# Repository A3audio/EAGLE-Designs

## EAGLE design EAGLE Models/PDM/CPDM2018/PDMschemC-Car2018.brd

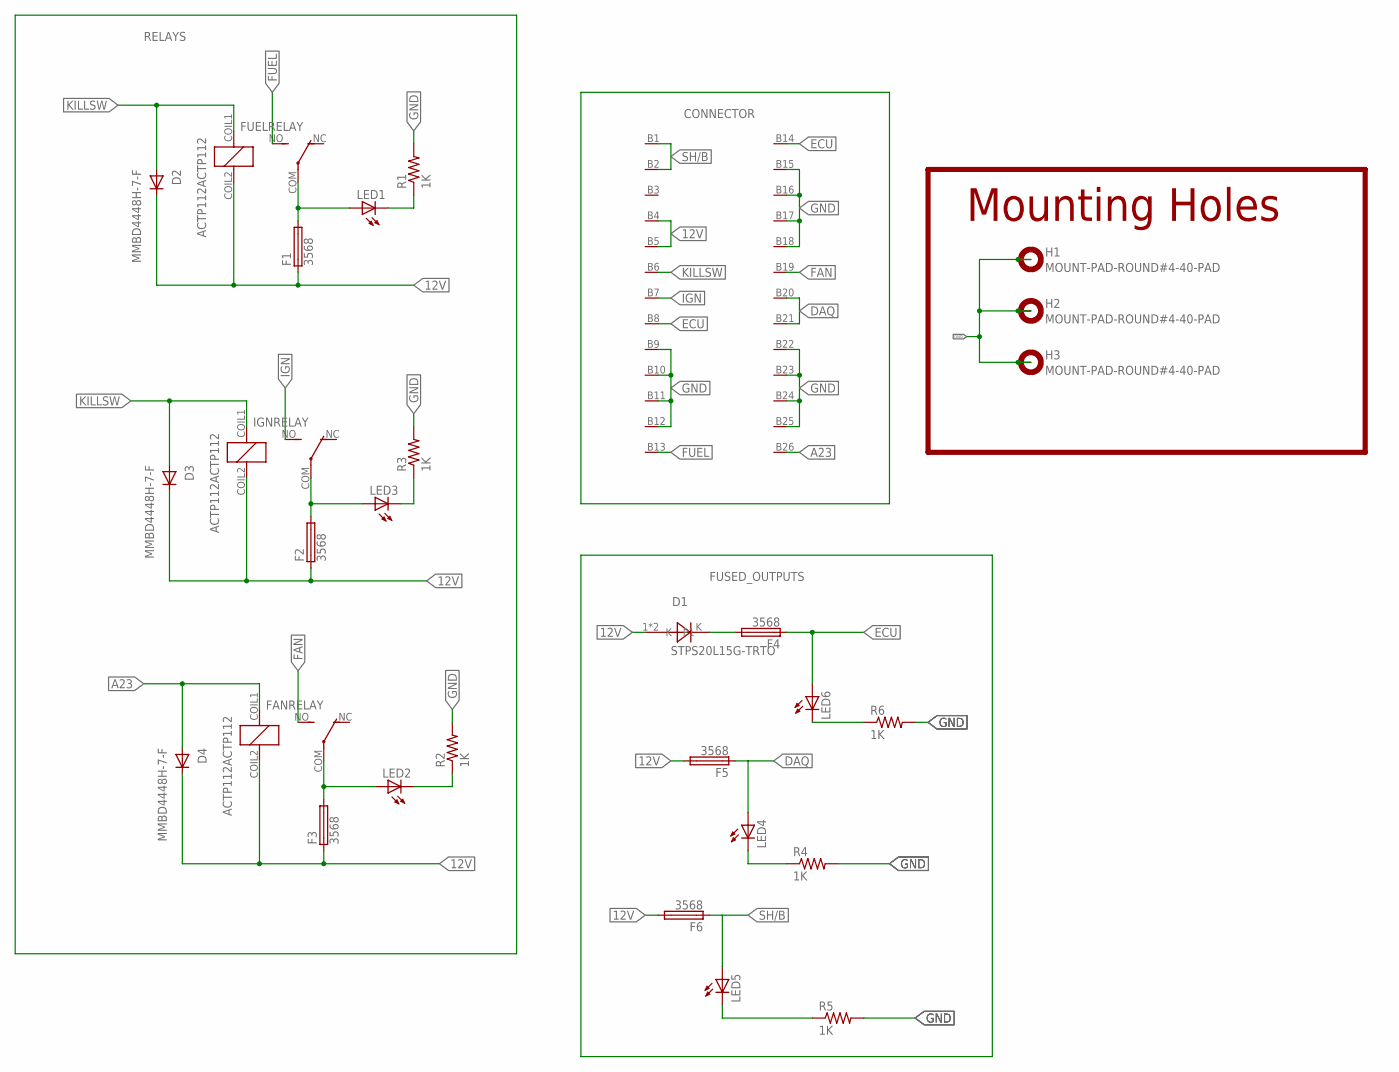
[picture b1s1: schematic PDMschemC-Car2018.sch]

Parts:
D1: STPS20L15G-TRTO; TO-262DIODE
D2, D3, D4: MMBD4448H-7-F; SOT23-3
F1, F2, F3, F4, F5, F6: 3568
FANRELAY: ACTP112ACTP112; ACTP112
FUELRELAY: ACTP112ACTP112; ACTP112
H1, H2, H3: MOUNT-PAD-ROUND#4-40-PAD; #4-40-PAD-ROUND
IGNRELAY: ACTP112ACTP112; ACTP112
LED1, LED2, LED3, LED4, LED5, LED6: LEDCHIPLED_0805; CHIPLED_0805
R1, R2, R3, R4, R5, R6: 1K; R0805
U$1: SUPERSEAL1.0_26POS

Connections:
12V: D1.1, D1.2 (P1), D2.3 (C), D3.3 (C), D4.3 (C), F1.1, F1.2 (1), F2.1, F2.2 (1), F3.1, F3.2 (1), F5.3 (2), F5.4 (2), F6.3 (2), F6.4 (2), FANRELAY.COIL2, FUELRELAY.COIL2, IGNRELAY.COIL2, U$1.B4, U$1.B5
A23: D4.1 (A), FANRELAY.COIL1, U$1.B26
DAQ: F5.1, F5.2 (1), LED4.A, U$1.B20, U$1.B21
ECU: F4.1, F4.2 (1), LED6.A, U$1.B8, U$1.B14
FAN: FANRELAY.NO, U$1.B19
FUEL: FUELRELAY.NO, U$1.B13
GND: H1.P$1, H2.P$1, H3.P$1, R1.2, R2.2, R3.2, R4.2, R5.2, R6.2, U$1.B9, U$1.B10, U$1.B11, U$1.B12, U$1.B15, U$1.B16, U$1.B17, U$1.B18, U$1.B22, U$1.B23, U$1.B24, U$1.B25
IGN: IGNRELAY.NO, U$1.B7
KILLSW: D2.1 (A), D3.1 (A), FUELRELAY.COIL1, IGNRELAY.COIL1, U$1.B6
unnamed: F3.3 (2), F3.4 (2), FANRELAY.COM, LED2.A
unnamed: LED1.C, R1.1
unnamed: F1.3 (2), F1.4 (2), FUELRELAY.COM, LED1.A
unnamed: LED2.C, R2.1
unnamed: LED3.C, R3.1
unnamed: F2.3 (2), F2.4 (2), IGNRELAY.COM, LED3.A
unnamed: LED4.C, R4.1
unnamed: LED6.C, R6.1
unnamed: D1.K, F4.3 (2), F4.4 (2)
unnamed: LED5.C, R5.1
SH/B: F6.1, F6.2 (1), LED5.A, U$1.B1, U$1.B2

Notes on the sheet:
Mounting Holes

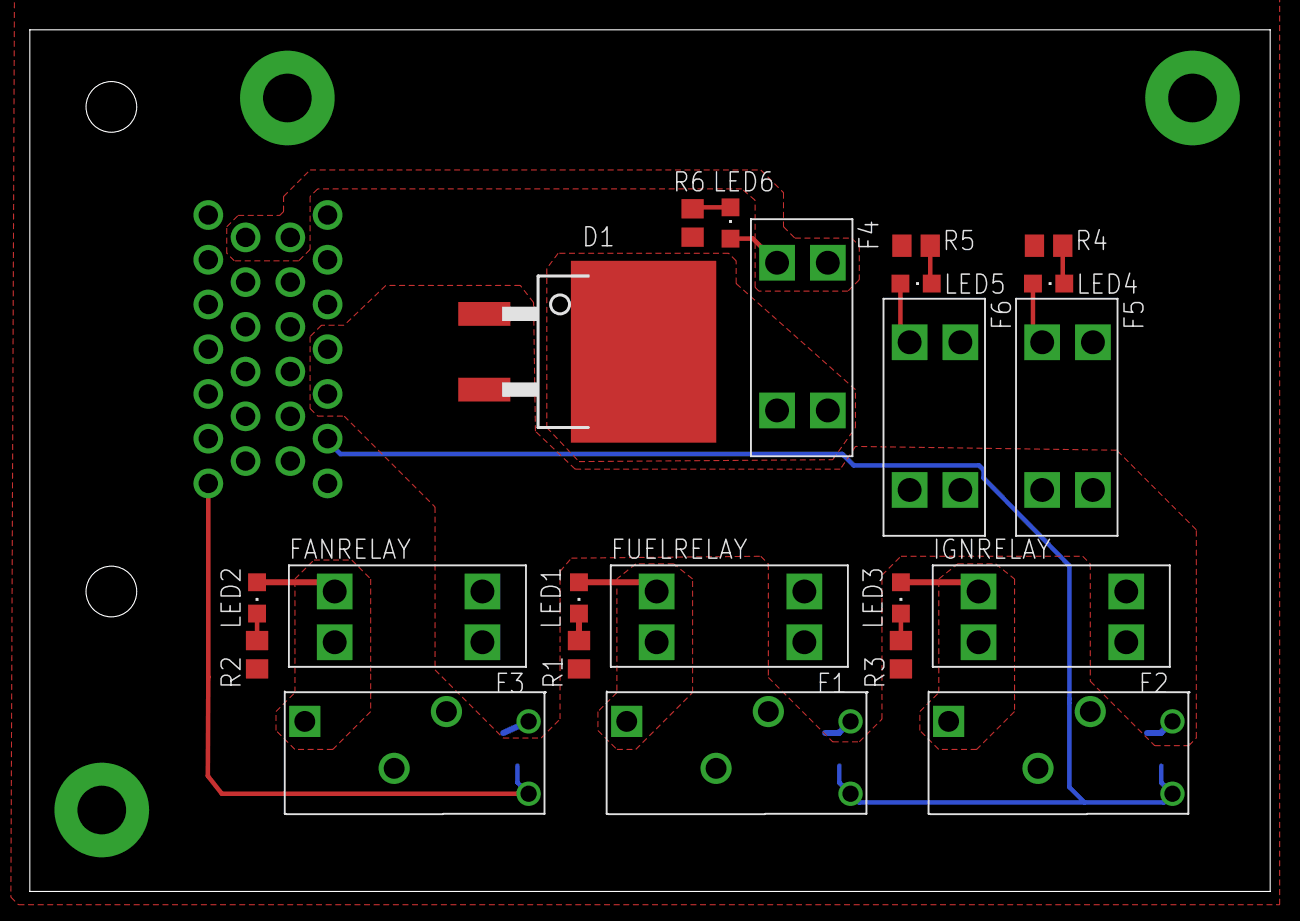
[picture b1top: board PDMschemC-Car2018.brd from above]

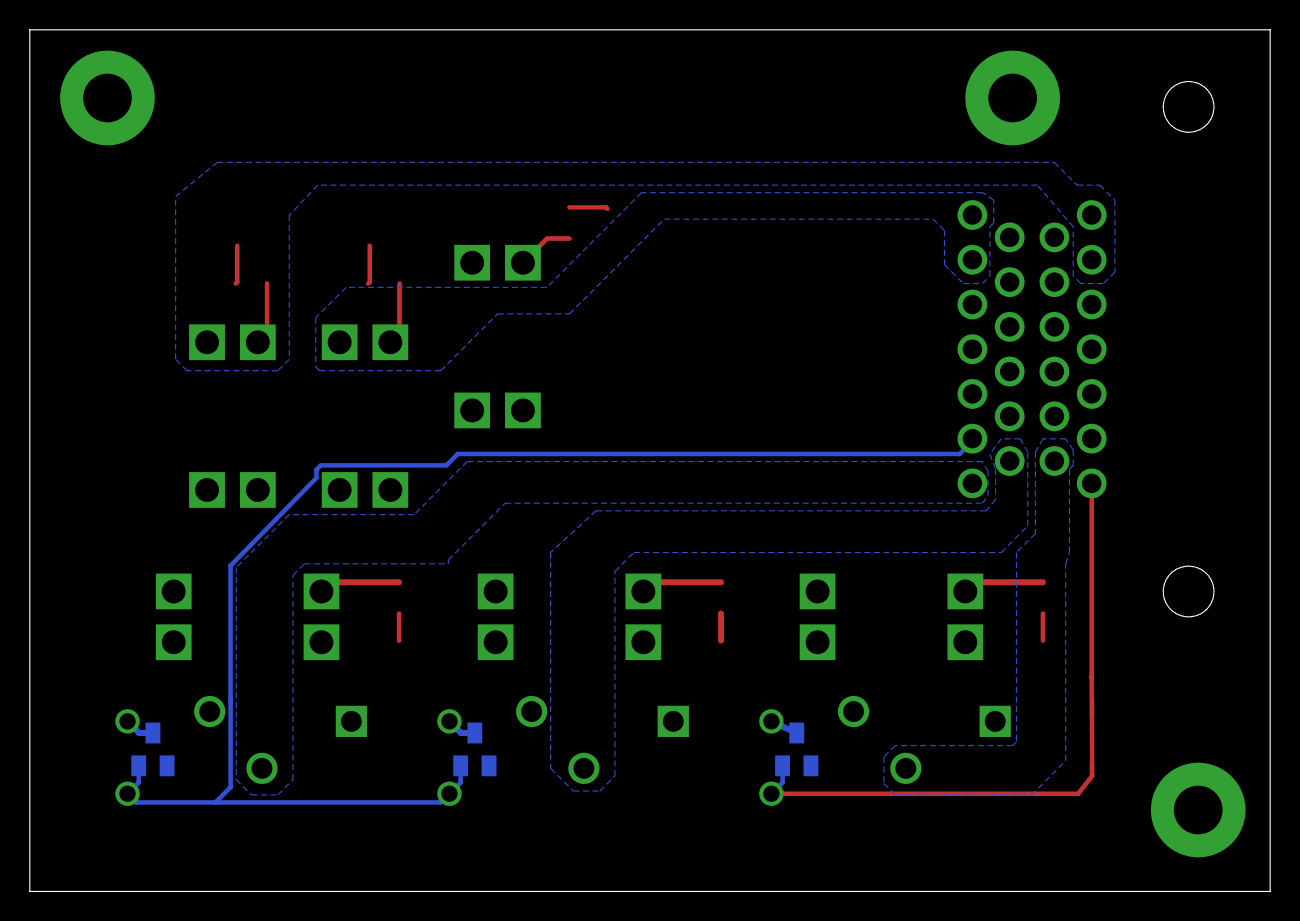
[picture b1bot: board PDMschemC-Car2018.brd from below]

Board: 2 copper layers, 83.2 x 57.8 mm, 29 parts (3 on the bottom side), 20 nets.

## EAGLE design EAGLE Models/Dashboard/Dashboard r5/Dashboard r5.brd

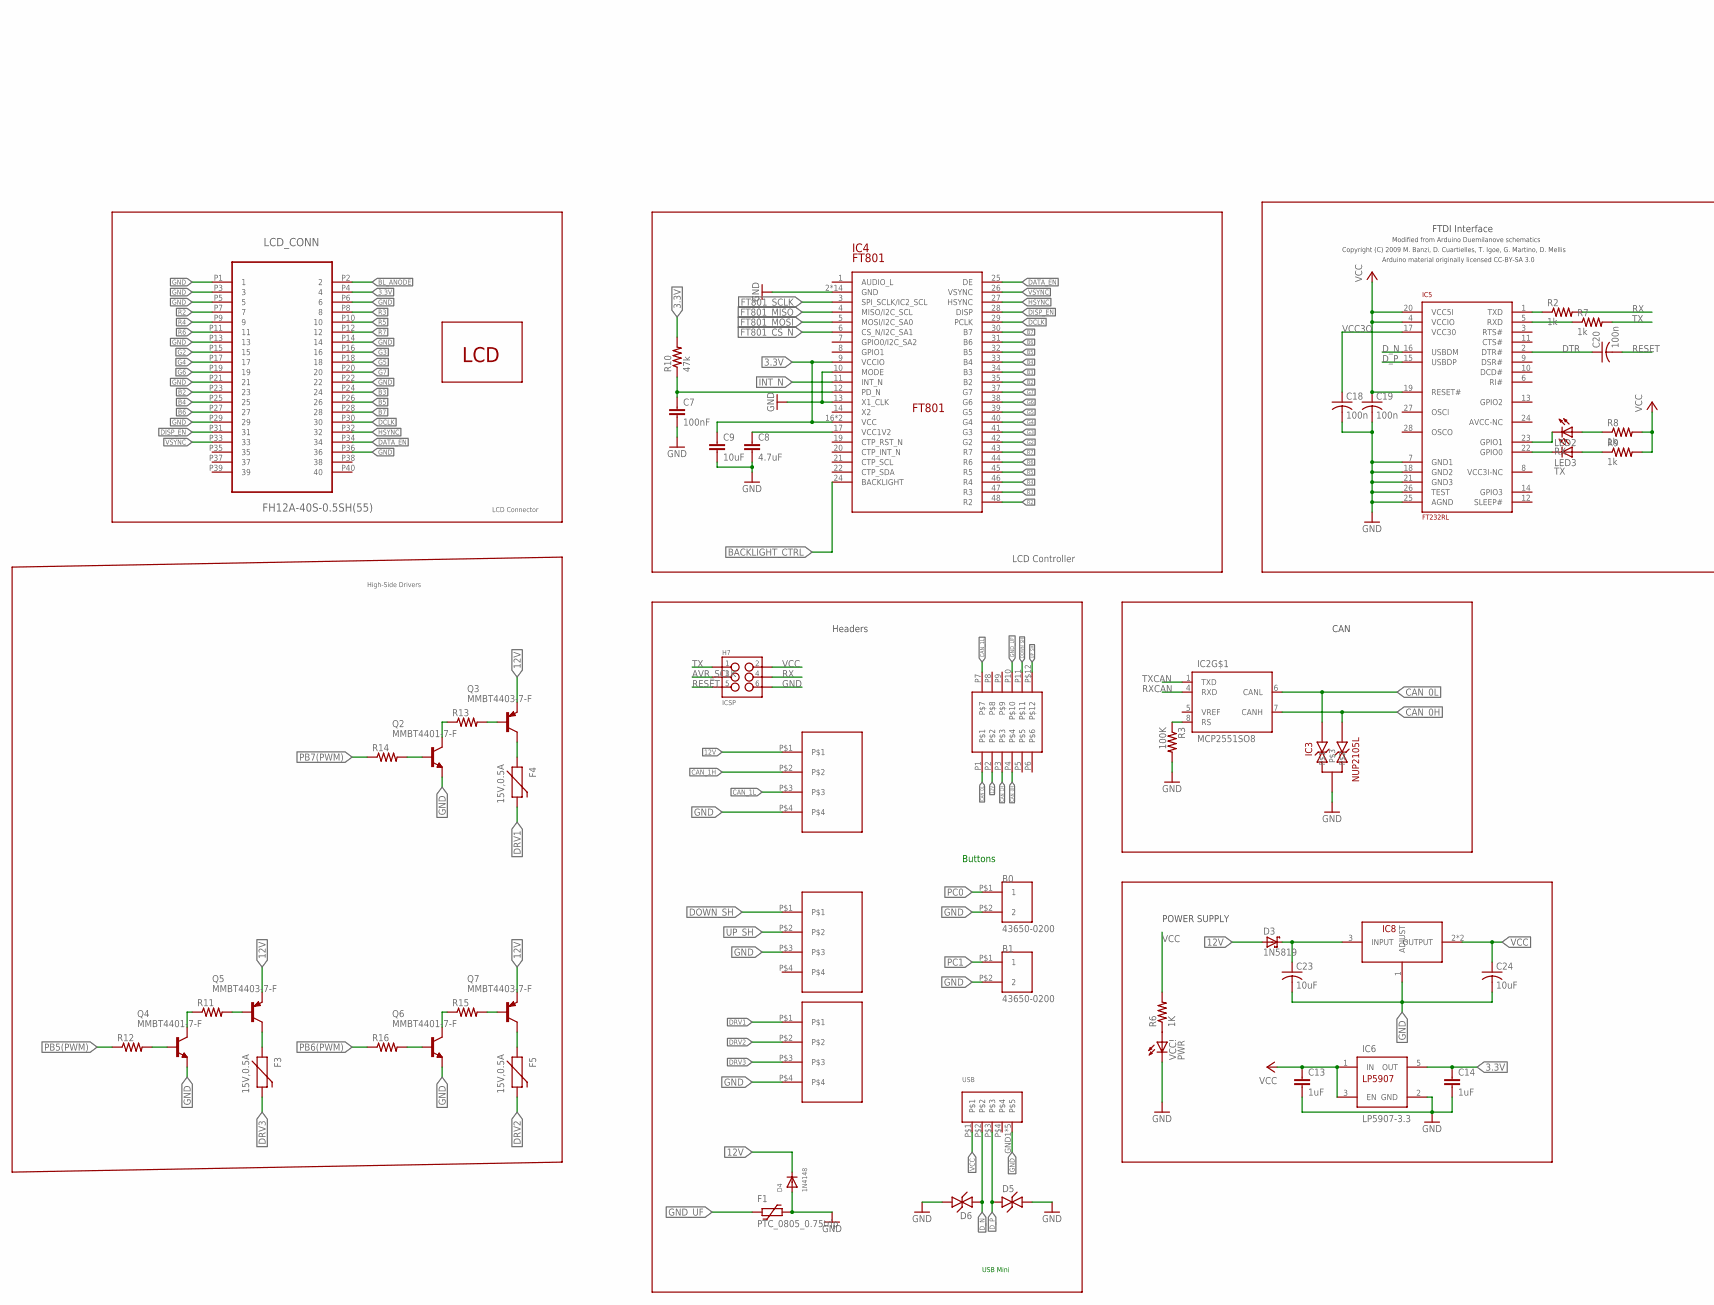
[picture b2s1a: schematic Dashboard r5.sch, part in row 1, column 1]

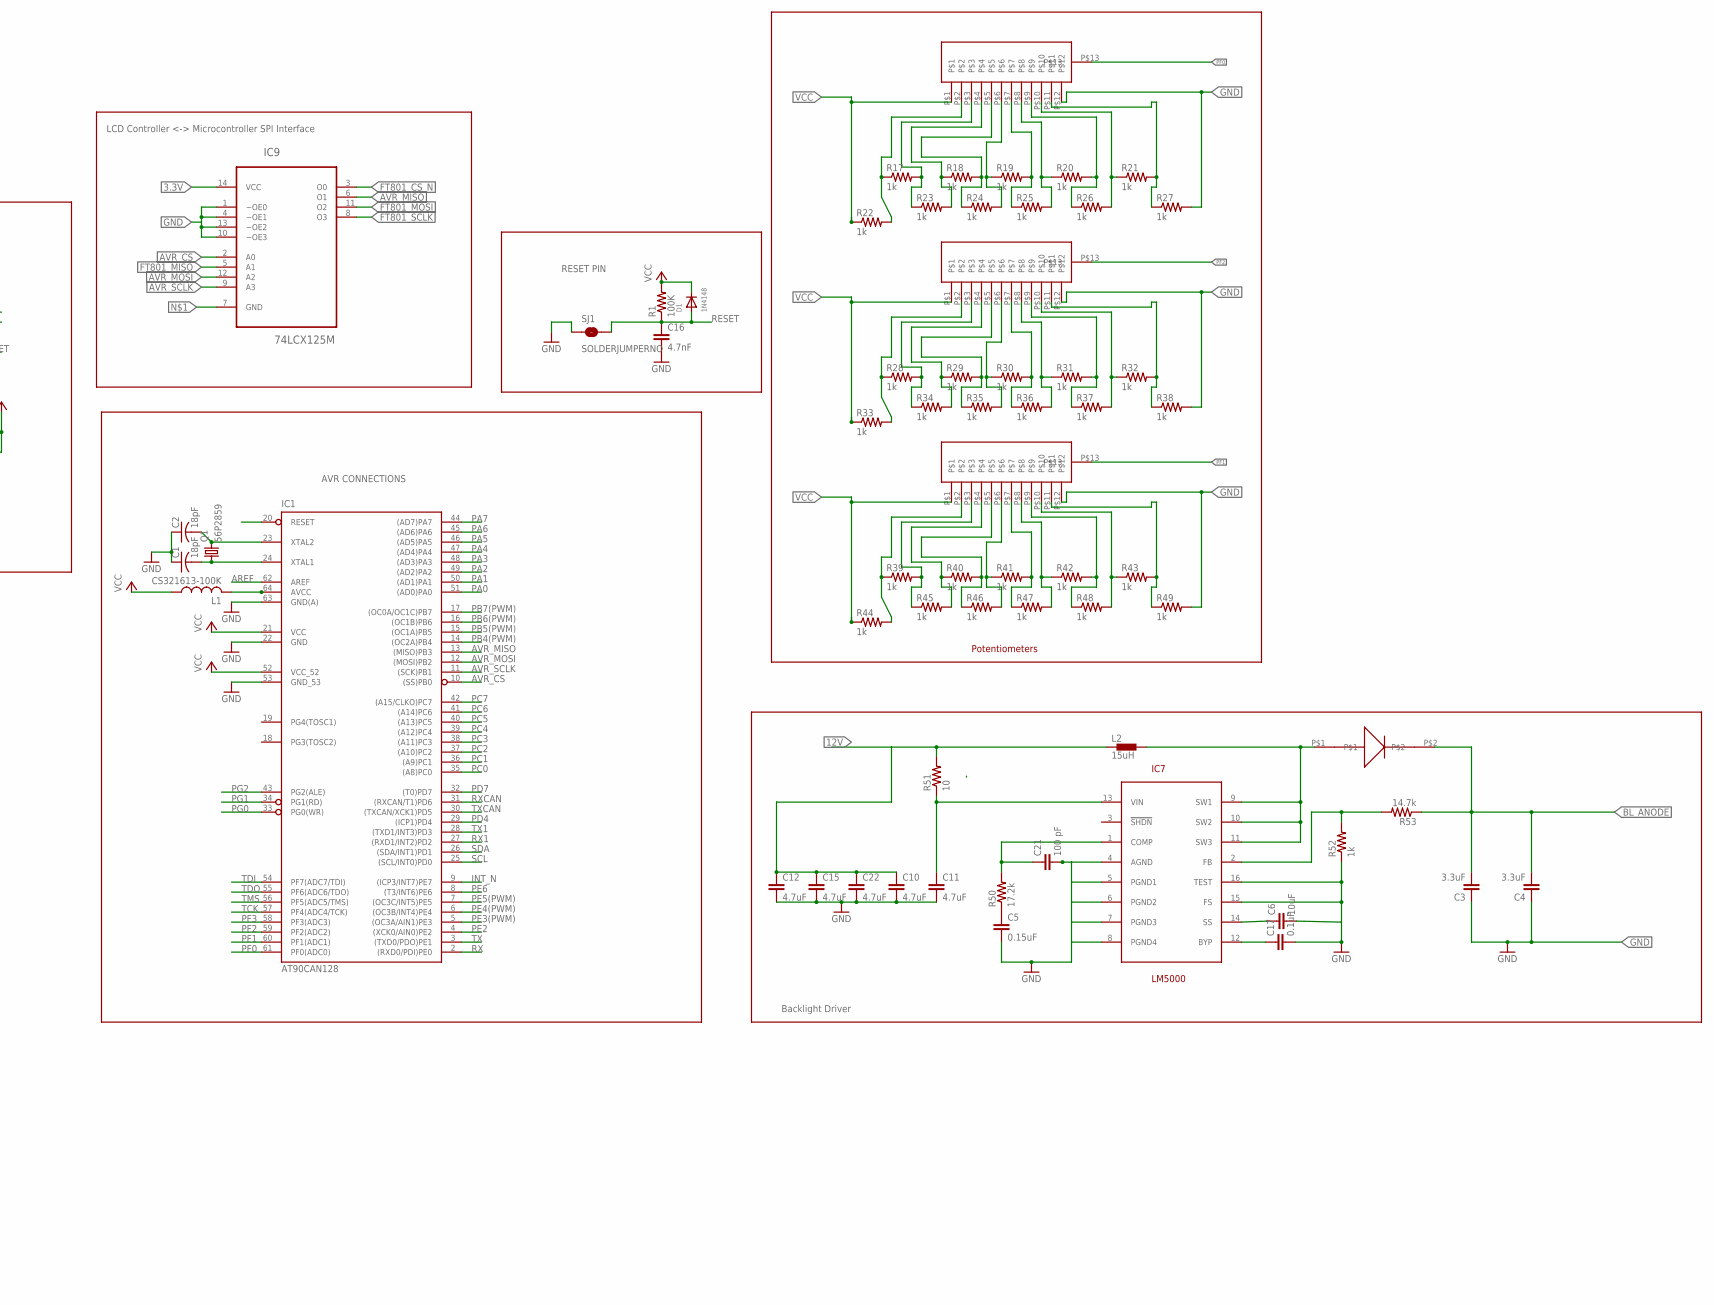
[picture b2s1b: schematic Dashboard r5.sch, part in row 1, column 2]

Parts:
B0, B1: 43650-0200; MOLEX_43650-0200
C1, C2: 18pF; C0805
C3, C4: 3.3uF; 0805
C5: 0.15uF; 0805
C6: 10uF; 0805
C7: 100nF; 0603-CAP
C8, C10, C11, C12, C15, C22: 4.7uF; 0805
C9: 10uF; 0603-CAP
C13, C14: 1uF; 0603-CAP
C16: 4.7nF; 0805
C17: 0.1uF; 0805
C18, C19, C20: 100n; C0805
C21: 100 pF; 0805
C23, C24: 10uF; C0603
CAN1: 043650-0409
D1, D4: 1N4148; SOD-123
D2: B160-FDICT_NB; B160-FDICT-NB
D3: 1N5819; SOD123
D5, D6: 24VM, 150VC, 0603; 0603
F1: PTC_0805_0.75trip; 0805L
F3, F4, F5: 15V,0.5A; PTC-1206
H7: ICSP; 2X3_SMD_FCI_54202-G30
IC1: AT90CAN128; TQFP64
IC2: MCP2551SO8; SO08
IC3: NUP2105L; SOT-23
IC4: FT801; RGZ48_5P15X5P15
IC5: FT232RL; SSOP28
IC6: LP5907-3.3; SOT23-DBV
IC7: LM5000
IC8: NCP1117; SOT-223-4
IC9: 74LCX125M; SOIC127P600X175-14N
J2: HR30-7R-12PD(71)
L1: CS321613-100K; L3216C
L2: 15uH; DEM8045C
LCD: TCG043WQLBAANN-GN00; TCG043WQLBAANN
LCD_CONN: FH12A-40S-0.5SH(55); HIROSE_FH12A-40S-0.5SH(55)
LED: 043650-0409
LED2: RX; CHIPLED_0805
LED3: TX; CHIPLED_0805
Q1: 56P2859; HC49UP
Q2, Q4, Q6: MMBT4401-7-F; SOT-23-3
Q3, Q5, Q7: MMBT4403-7-F; SOT-23-3
R1, R3: 100K; R0805
R2, R7, R8, R9: 1k; R0805
R6: 1K; R0805
R10: 47k; 0603-RES
R11, R12, R13, R14, R15, R16: RESISTOR0603; 0603-RES
R17, R18, R19, R20, R21, R22, R23, R24, R25, R26, R27, R28, R29, R30, R31, R32, R33, R34, R35, R36, R37, R38, R39, R40, R41, R42, R43, R44, R45, R46, R47, R48, R49: 1k; R0603
R50: 17.2k; 0805
R51: 10; 0603-RES
R52: 1k; 0603-RES
R53: 14.7k; 0603-RES
S1, S2, S3: ROTSWITCH
SHIFT: 043650-0409
SJ1: SOLDERJUMPERNO; SJ_2S-NO
USB: 67503-1020; MOLEX_67503-1020
VCC!: PWR; CHIPLED_0805

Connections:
3.3V: C9.1, C14.1, IC4.9 (VCCIO), IC4.16 (VCC), IC4.18 (VCC), IC6.5 (OUT), IC9.14 (VCC), LCD_CONN.P4 (4), R10.2
5V_REG_IN: C23.1, D3.C, IC8.3 (INPUT)
12V: C10.1, C12.1, C15.1, C22.1, CAN1.P$1, D3.A, D4.C, J2.P2, L2.P$1 (1), Q3.P$3 (E), Q5.P$3 (E), Q7.P$3 (E), R51.2
AREF: IC1.62 (AREF)
AVR_CS: IC1.10 ((SS)PB0), IC9.2 (A0)
AVR_MISO: IC1.13 ((MISO)PB3), IC9.6 (O1)
AVR_MOSI: IC1.12 ((MOSI)PB2), IC9.12 (A2)
AVR_SCLK: H7.3, IC1.11 ((SCK)PB1), IC9.9 (A3)
B2: IC4.35 (B2), LCD_CONN.P23 (23)
B3: IC4.34 (B3), LCD_CONN.P24 (24)
B4: IC4.33 (B4), LCD_CONN.P25 (25)
B5: IC4.32 (B5), LCD_CONN.P26 (26)
B6: IC4.31 (B6), LCD_CONN.P27 (27)
B7: IC4.30 (B7), LCD_CONN.P28 (28)
BACKLIGHT_CTRL: IC4.24 (BACKLIGHT)
BL_ANODE: C3.2, C4.2, D2.P$2, LCD_CONN.P2 (2), R53.1
CAN_0H: IC2.7 (CANH), IC3.2, J2.P4
CAN_0L: IC2.6 (CANL), IC3.1, J2.P1
CAN_1H: CAN1.P$2, J2.P3
CAN_1L: CAN1.P$3, J2.P7
DATA_EN: IC4.25 (DE), LCD_CONN.P34 (34)
DCLK: IC4.29 (PCLK), LCD_CONN.P30 (30)
DISP_EN: IC4.28 (DISP), LCD_CONN.P31 (31)
DOWN_SH: J2.P11, SHIFT.P$1
DRV1: F4.2, LED.P$1
DRV2: F5.2, LED.P$2
DRV3: F3.2, LED.P$3
DTR: C20.1, IC5.2 (DTR#)
D_N: D6.1, IC5.16 (USBDM), USB.P$2
D_P: D5.1, IC5.15 (USBDP), USB.P$3
FT801_CS_N: IC4.6 (CS_N/I2C_SA1), IC9.3 (O0)
FT801_MISO: IC4.4 (MISO/I2C_SCL), IC9.5 (A1)
FT801_MOSI: IC4.5 (MOSI/I2C_SA0), IC9.11 (O2)
FT801_SCLK: IC4.3 (SPI_SCLK/IC2_SCL), IC9.8 (O3)
G2: IC4.42 (G2), LCD_CONN.P15 (15)
G3: IC4.41 (G3), LCD_CONN.P16 (16)
G4: IC4.40 (G4), LCD_CONN.P17 (17)
G5: IC4.39 (G5), LCD_CONN.P18 (18)
G6: IC4.38 (G6), LCD_CONN.P19 (19)
G7: IC4.37 (G7), LCD_CONN.P20 (20)
GND: B0.P$2 (2), B1.P$2 (2), C1.1, C2.1, C3.1, C4.1, C5.2, C6.2, C7.2, C8.2, C9.2, C10.2, C11.2, C12.2, C13.2, C14.2, C15.2, C16.2, C17.2, C18.2, C19.2, C21.2, C22.2, C23.2, C24.2, CAN1.P$4, D4.A, D5.2, D6.2, F1.1, H7.6, IC1.22 (GND), IC1.53 (GND_53), IC1.63 (GND(A)), IC2.2 (GND), IC3.3, IC4.2 (GND), IC4.10 (MODE), IC4.13 (X1_CLK), IC4.15 (GND), IC4.23 (GND), IC4.36 (GND), IC4.EP (GND), IC4.V_1 (GND), IC4.V_2 (GND), IC4.V_3 (GND), IC4.V_4 (GND), IC4.V_5 (GND), IC4.V_6 (GND), IC4.V_7 (GND), IC4.V_8 (GND), IC4.V_9 (GND), IC5.7 (GND1), IC5.18 (GND2), IC5.21 (GND3), IC5.25 (AGND), IC5.26 (TEST), IC6.2 (GND), IC7.4 (AGND), IC7.5 (PGND1), IC7.6 (PGND2), IC7.7 (PGND3), IC7.8 (PGND4), IC7.15 (FS), IC7.16 (TEST), IC8.1 (ADJUST), IC9.1 (~OE0), IC9.4 (~OE1), IC9.10 (~OE3), IC9.13 (~OE2), LCD_CONN.P1 (1), LCD_CONN.P3 (3), LCD_CONN.P5 (5), LCD_CONN.P6 (6), LCD_CONN.P13 (13), LCD_CONN.P14 (14), LCD_CONN.P21 (21), LCD_CONN.P22 (22), LCD_CONN.P29 (29), LCD_CONN.P36 (36), LED.P$4, Q2.P$3 (E), Q4.P$3 (E), Q6.P$3 (E), R3.2, R27.2, R38.2, R49.2, R52.1, S1.P$12, S2.P$12, S3.P$12, SHIFT.P$3, SJ1.1, USB.GND1, USB.GND2, USB.GND3, USB.GND4, USB.P$5, VCC!.C
GND_UF: F1.2, J2.P10
HSYNC: IC4.27 (HSYNC), LCD_CONN.P32 (32)
INT_N: IC1.9 ((ICP3/INT7)PE7), IC4.11 (INT_N)
M8RXD: IC5.1 (TXD), R2.1
M8TXD: IC5.5 (RXD), R7.1
unnamed: C8.1, IC4.17 (VCC1V2)
unnamed: C7.1, IC4.12 (PD_N), R10.1
unnamed: C5.1, R50.1
unnamed: IC2.8 (RS), R3.1
unnamed: R6.1, VCC!.A
unnamed: C1.2, IC1.24 (XTAL1), Q1.1
unnamed: IC1.64 (AVCC), L1.2
unnamed: Q4.P$2 (B), R12.2
unnamed: Q5.P$2 (B), R11.2
unnamed: Q4.P$1 (C), R11.1
unnamed: F3.1, Q5.P$1 (C)
unnamed: Q2.P$2 (B), R14.2
unnamed: IC5.23 (GPIO1), LED2.C
unnamed: Q3.P$2 (B), R13.2
unnamed: IC5.22 (GPIO0), LED3.C
unnamed: LED2.A, R8.1
unnamed: LED3.A, R9.1
unnamed: Q2.P$1 (C), R13.1
unnamed: F4.1, Q3.P$1 (C)
unnamed: Q6.P$2 (B), R16.2
unnamed: Q7.P$2 (B), R15.2
unnamed: Q6.P$1 (C), R15.1
unnamed: F5.1, Q7.P$1 (C)
unnamed: R17.1, R22.2, S1.P$2
unnamed: R17.2, R23.1, S1.P$3
unnamed: R18.1, R23.2, S1.P$4
unnamed: R18.2, R24.1, S1.P$5
unnamed: R20.1, R25.2, S1.P$8
unnamed: R20.2, R26.1, S1.P$9
unnamed: R19.1, R24.2, S1.P$6
unnamed: R19.2, R25.1, S1.P$7
unnamed: R21.1, R26.2, S1.P$10
unnamed: R28.1, R33.2, S2.P$2
unnamed: R21.2, R27.1, S1.P$11
unnamed: R28.2, R34.1, S2.P$3
unnamed: R29.1, R34.2, S2.P$4
unnamed: R29.2, R35.1, S2.P$5
unnamed: R31.1, R36.2, S2.P$8
unnamed: R31.2, R37.1, S2.P$9
unnamed: R30.1, R35.2, S2.P$6
unnamed: R30.2, R36.1, S2.P$7
unnamed: R32.1, R37.2, S2.P$10
unnamed: R32.2, R38.1, S2.P$11
unnamed: R39.1, R44.2, S3.P$2
unnamed: R39.2, R45.1, S3.P$3
unnamed: R40.1, R45.2, S3.P$4
unnamed: R40.2, R46.1, S3.P$5
unnamed: R42.1, R47.2, S3.P$8
unnamed: R42.2, R48.1, S3.P$9
unnamed: R41.1, R46.2, S3.P$6
unnamed: R41.2, R47.1, S3.P$7
unnamed: R43.1, R48.2, S3.P$10
unnamed: R43.2, R49.1, S3.P$11
unnamed: C21.1, IC7.1 (COMP), R50.2
unnamed: C11.1, IC7.13 (VIN), R51.1
unnamed: D2.P$1, IC7.9 (SW1), IC7.10 (SW2), IC7.11 (SW3), L2.P$2 (2)
unnamed: IC7.2 (FB), R52.2, R53.2
unnamed: C6.1, IC7.14 (SS)
unnamed: C17.1, IC7.12 (BYP)
PA0: IC1.51 ((AD0)PA0)
PA1: IC1.50 ((AD1)PA1)
PA2: IC1.49 ((AD2)PA2)
PA3: IC1.48 ((AD3)PA3)
PA4: IC1.47 ((AD4)PA4)
PA5: IC1.46 ((AD5)PA5)
PA6: IC1.45 ((AD6)PA6)
PA7: IC1.44 ((AD7)PA7)
PB4(PWM): IC1.14 ((OC2A)PB4)
PB5(PWM): IC1.15 ((OC1A)PB5), R12.1
PB6(PWM): IC1.16 ((OC1B)PB6), R16.1
PB7(PWM): IC1.17 ((OC0A/OC1C)PB7), R14.1
PC0: B0.P$1 (1), IC1.35 ((A8)PC0)
PC1: B1.P$1 (1), IC1.36 ((A9)PC1)
PC2: IC1.37 ((A10)PC2)
PC3: IC1.38 ((A11)PC3)
PC4: IC1.39 ((A12)PC4)
PC5: IC1.40 ((A13)PC5)
PC6: IC1.41 ((A14)PC6)
PC7: IC1.42 ((A15/CLKO)PC7)
PD4: IC1.29 ((ICP1)PD4)
PD7: IC1.32 ((T0)PD7)
PE2: IC1.4 ((XCK0/AIN0)PE2)
PE3(PWM): IC1.5 ((OC3A/AIN1)PE3)
PE4(PWM): IC1.6 ((OC3B/INT4)PE4)
PE5(PWM): IC1.7 ((OC3C/INT5)PE5)
PE6: IC1.8 ((T3/INT6)PE6)
PF0: IC1.61 (PF0(ADC0)), S1.P$13
PF1: IC1.60 (PF1(ADC1)), S3.P$13
PF2: IC1.59 (PF2(ADC2)), S2.P$13
PF3: IC1.58 (PF3(ADC3))
PG0: IC1.33 (PG0(WR))
PG1: IC1.34 (PG1(RD))
PG2: IC1.43 (PG2(ALE))
R2: IC4.48 (R2), LCD_CONN.P7 (7)
R3: IC4.47 (R3), LCD_CONN.P8 (8)
R4: IC4.46 (R4), LCD_CONN.P9 (9)
R5: IC4.45 (R5), LCD_CONN.P10 (10)
R6: IC4.44 (R6), LCD_CONN.P11 (11)
R7: IC4.43 (R7), LCD_CONN.P12 (12)
RESET: C16.1, C20.2, D1.A, H7.5, IC1.20 (RESET), R1.1, SJ1.2
RX: H7.4, IC1.2 ((RXD0/PDI)PE0), R2.2
RX1: IC1.27 ((RXD1/INT2)PD2)
RXCAN: IC1.31 ((RXCAN/T1)PD6), IC2.4 (RXD)
SCL: IC1.25 ((SCL/INT0)PD0)
SDA: IC1.26 ((SDA/INT1)PD1)
TCK: IC1.57 (PF4(ADC4/TCK))
TDI: IC1.54 (PF7(ADC7/TDI))
TDO: IC1.55 (PF6(ADC6/TDO))
TMS: IC1.56 (PF5(ADC5/TMS))
TX: H7.1, IC1.3 ((TXD0/PDO)PE1), R7.2
TX1: IC1.28 ((TXD1/INT3)PD3)
TXCAN: IC1.30 ((TXCAN/XCK1)PD5), IC2.1 (TXD)
UP_SH: J2.P$12, SHIFT.P$2
VCC: C13.1, C19.1, C24.1, D1.C, H7.2, IC1.21 (VCC), IC1.52 (VCC_52), IC2.3 (VCC), IC5.4 (VCCIO), IC5.19 (RESET#), IC5.20 (VCC5I), IC6.1 (IN), IC6.3 (EN), IC8.2 (OUTPUT), IC8.4 (OUTPUT), L1.1, R1.2, R6.2, R8.2, R9.2, R22.1, R33.1, R44.1, S1.P$1, S2.P$1, S3.P$1, USB.P$1
VCC3O: C18.1, IC5.17 (VCC30)
VSYNC: IC4.26 (VSYNC), LCD_CONN.P33 (33)
XTAL1: C2.2, IC1.23 (XTAL2), Q1.2

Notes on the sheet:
POWER SUPPLY
CAN
RESET PIN
AVR CONNECTIONS
FTDI Interface
Headers
Modified from Arduino Duemilanove schematics
Copyright (C) 2009 M. Banzi, D. Cuartielles, T. Igoe, G. Martino, D. Mellis
Arduino material originally licensed CC-BY-SA 3.0
LCD Controller
LCD Controller <-> Microcontroller SPI Interface
Backlight Driver
LCD Connector
High-Side Drivers
Potentiometers
Buttons
USB Mini

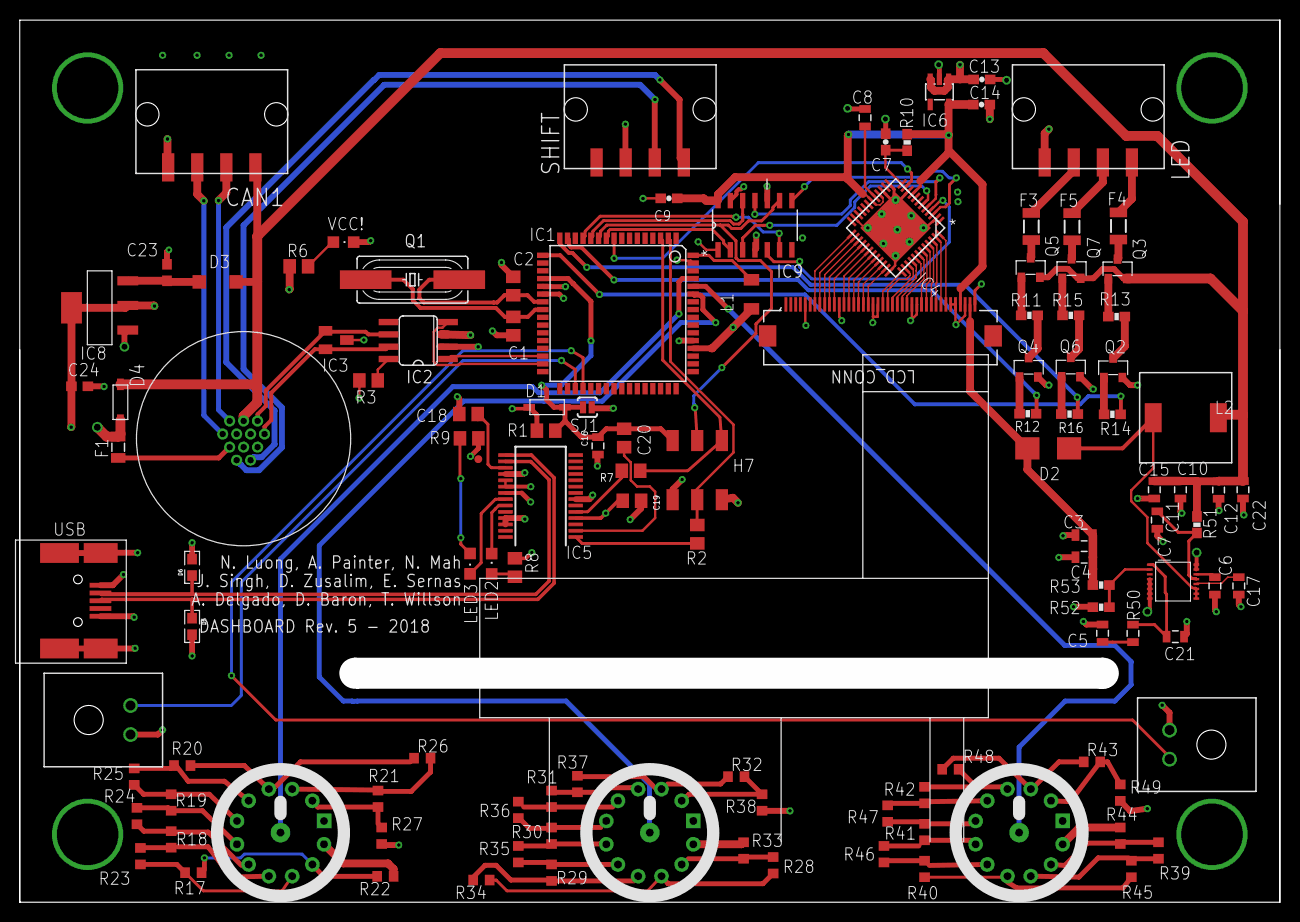
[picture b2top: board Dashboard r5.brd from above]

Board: 4 copper layers, 130.0 x 91.0 mm, 120 parts (0 on the bottom side), 127 nets.

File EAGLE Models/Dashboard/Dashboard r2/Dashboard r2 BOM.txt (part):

Partlist exported from C:/Users/Daniel Baron/Desktop/FSAE2016Boards and Schematics/Dashboard12-12.sch at 1/12/2016 12:52 PM

Part     Value               Device              Package                    Description                                                                         MPN                 OC_FARNELL OC_NEWARK PACKAGE                           SUPPLIER 
BL_D1    DFLS1100-7          DFLS1100-7          POWERDI-123                                                                                                                                                                                        
BL_L1    47uH                LTF4022-D           2-SMD                      LTF4022                                                                                                                                                                 
C1       18pF                C-USC0805           C0805                      CAPACITOR, American symbol                                                                                                                                              
C2       18pF                C-USC0805           C0805                      CAPACITOR, American symbol                                                                                                                                              
C3       22uF                C-USC2220           C2220                      CAPACITOR, American symbol                                                                                                                                              
C4       22uF                C-USC2220           C2220                      CAPACITOR, American symbol                                                                                                                                              
C7       100nF               CAP0603-CAP         0603-CAP                   Capacitor                                                                                                                                                               
C8       4.7uF               CAP0805             0805                       Capacitor                                                                                                                                                               
C9       10uF                C-USC2220           C2220                      CAPACITOR, American symbol                                                                                                                                              
C12      100n                C-USC0805           C0805                      CAPACITOR, American symbol                                                                                                                                              
C13      1uF                 CAP0603-CAP         0603-CAP                   Capacitor                                                                                                                                                               
C14      1uF                 CAP0603-CAP         0603-CAP                   Capacitor                                                                                                                                                               
C15      10uF                C-USC2220           C2220                      CAPACITOR, American symbol                                                                                                                                              
C16      4.7nF               CAP0805             0805                       Capacitor                                                                                                                                                               
C18      100n                C-USC0805           C0805                      CAPACITOR, American symbol                                                                                                                                              
C19      100n                C-USC0805           C0805                      CAPACITOR, American symbol                                                                                                                                              
C20      100n                C-USC0805           C0805                      CAPACITOR, American symbol                                                                                                                                              
CANPWR   MICRO5LOCK          MICRO5LOCK          MICRO5LOCK                                                                                                                                                                                         
CDHC     390nF               CAP0603-CAP         0603-CAP                   Capacitor                                                                                                                                                               
CFB      10.0pF              CAP0603-CAP         0603-CAP                   Capacitor                                                                                                                                                               
CIN      4.7uF               CAP0805             0805                       Capacitor                                                                                                                                                               
CIN1     4.7uF               CAP0805             0805                       Capacitor                                                                                                                                                               
CIN2     4.7uF               CAP0805             0805                       Capacitor                                                                                                                                                               
CIN3     4.7uF               CAP0805             0805                       Capacitor                                                                                                                                                               
COUT     120nF               CAP0805             0805                       Capacitor                                                                                                                                                               
CVCC     1uF                 CAP0603-CAP         0603-CAP                   Capacitor                                                                                                                                                               
D1       1N4148              DIODESOD-123        SOD-123                    Diode                                                                                                                                                                   
D2       1N5819              1N5819-BSOD123      SOD123                     1.0A SCHOTTKY BARRIER RECTIFIER                                                                                                                                         
F1       16V,0.25A           PTCSMD              PTC-1206                   Resettable Fuse PTC                                                                                                                                                     
F2       15V,0.5A            PTCSMD              PTC-1206                   Resettable Fuse PTC                                                                                                                                                     
F3       15V,0.5A            PTCSMD              PTC-1206                   Resettable Fuse PTC                                                                                                                                                     
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

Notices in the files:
parts and their libraries:
SparkFun-Passives: Licensing: CC v3.0 Share-Alike You are welcome to use this library for commercial purposes.
